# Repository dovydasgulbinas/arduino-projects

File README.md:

# arduino-projects
a series of majority of my arduino projects

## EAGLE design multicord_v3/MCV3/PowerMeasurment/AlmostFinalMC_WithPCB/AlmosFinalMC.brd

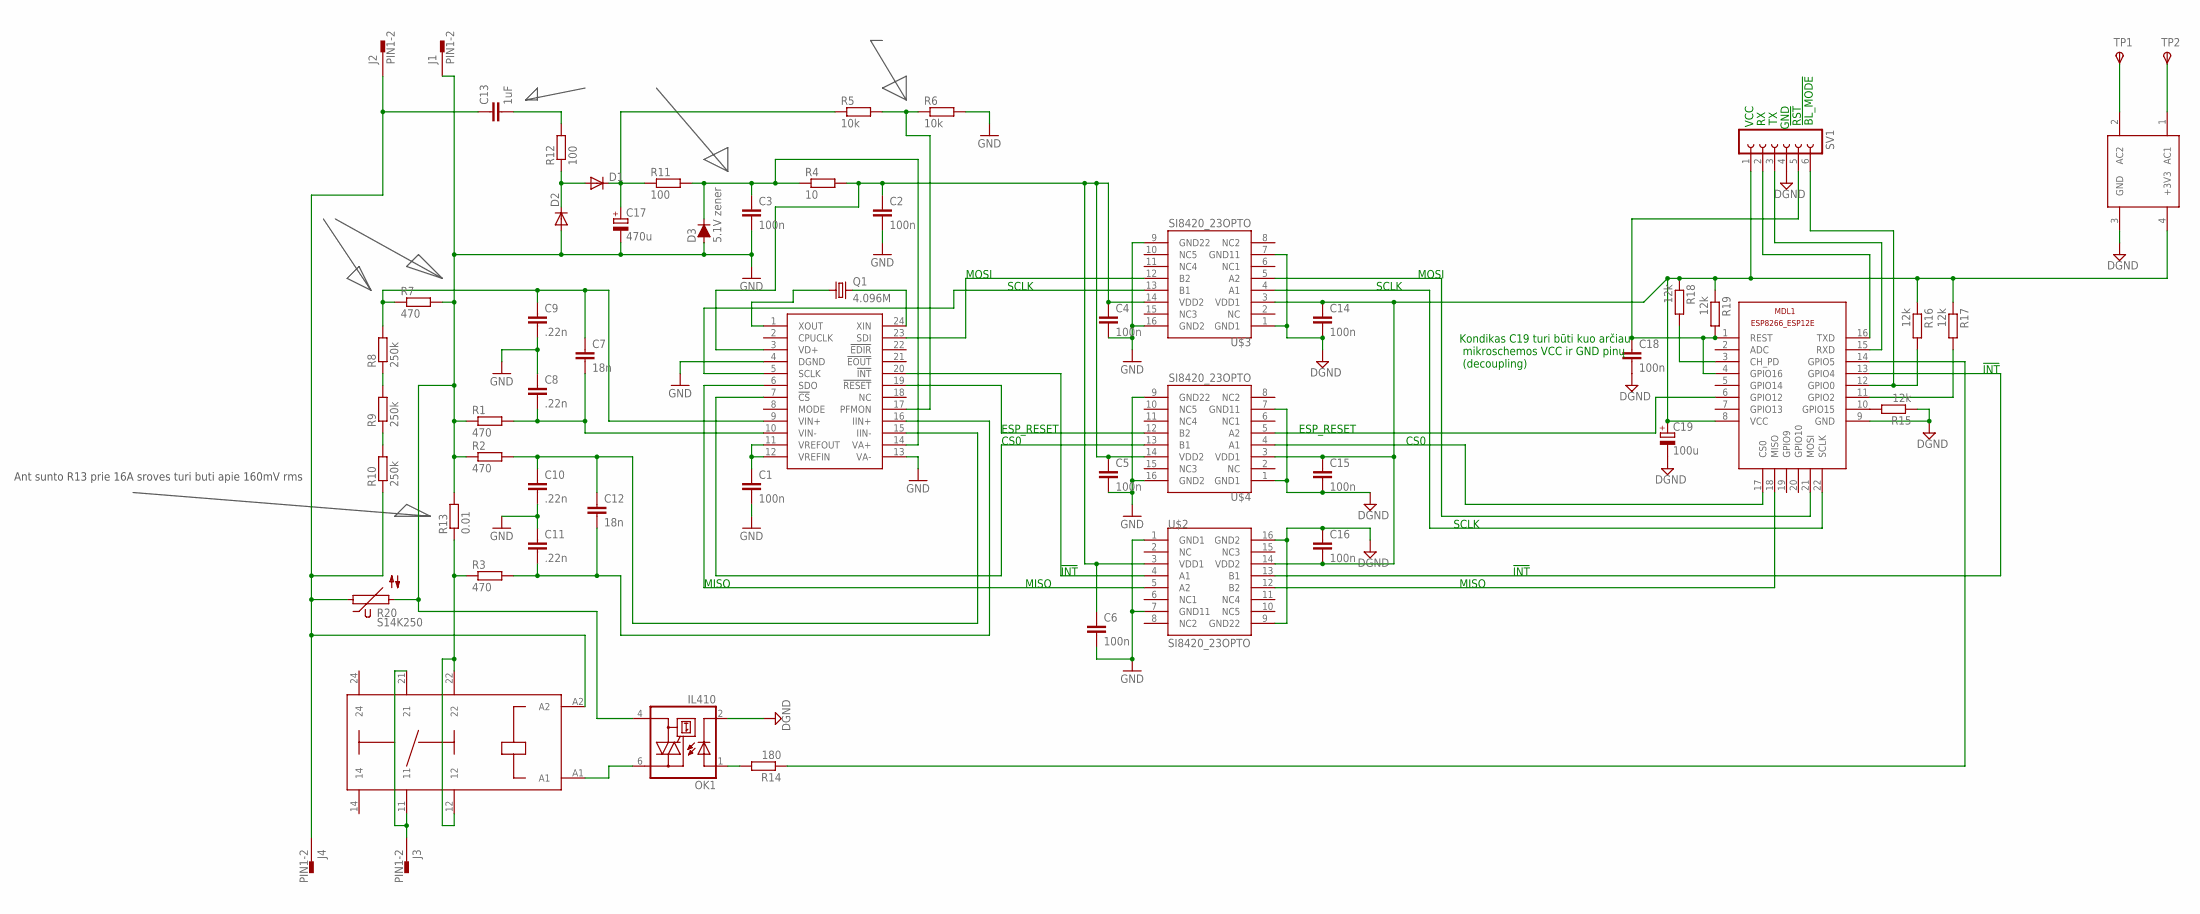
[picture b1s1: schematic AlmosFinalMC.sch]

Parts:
C1, C2, C3, C4, C5, C6, C14, C15, C16, C18: 100n; C0805
C7, C12: 18n; C0805
C8, C9, C10, C11: .22n; C0805
C13: 1uF; C225-113X268
C17: 470u; PANASONIC_G
C19: 100u; PANASONIC_G
D1, D2: DIODE-DO-214AC; DO-214AC
D3: 5.1V zener; SOD123
J1, J2, J3, J4: PIN1-2; 62221
MDL1: ESP8266-12EESP8266-ESP12E; ESP8266-ESP12E
OK1: IL410; DIL06
Q1: 4.096M; HC49UP
R1, R2, R3, R7: 470; R0805
R4: 10; R0805
R5, R6: 10k; R0805
R8, R9, R10: 250k; 0204/5
R11: 100; 0207/5V
R12: 100; 0309/10
R13: 0.01; RDH/15
R14: 180; R0805
R15, R16, R17, R18, R19: 12k; R0805
R20: S14K250
SV1: FE06-1; FE06
TP1, TP2: TPSPAD1-20Y; P1-20Y
U$1: CS5460A; SSOP24
U$2, U$3, U$4: SI8420_23OPTO; SI8420-SOIC8WB
U$5: RAC02
U$6: FINDER40-61

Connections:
DGND: C14.2, C15.2, C16.1, C18.2, C19.-, MDL1.9 (GND), OK1.2 (C), R15.1, SV1.4, U$2.9 (GND22), U$2.16 (GND2), U$3.1 (GND1), U$3.7 (GND11), U$4.1 (GND1), U$4.7 (GND11), U$5.3 (GND)
GND: C1.2, C2.2, C3.2, C4.2, C5.2, C6.2, C8.1, C9.2, C10.2, C11.1, C17.-, D2.A, D3.2 (A), J1.1, OK1.4 (A1), R1.1, R2.1, R6.2, R7.2, R13.2, R20.2, U$1.4 (DGND), U$1.13 (VA-), U$2.1 (GND1), U$2.7 (GND11), U$3.9 (GND22), U$3.16 (GND2), U$4.9 (GND22), U$4.16 (GND2)
unnamed: C3.1, D3.1 (C), R4.1, R11.2, U$1.14 (VA+)
unnamed: C2.1, C4.1, C5.1, C6.1, R4.2, U$1.3 (VD+), U$2.3 (VDD1), U$3.14 (VDD2), U$4.14 (VDD2)
unnamed: R5.2, R6.1, U$1.17 (PFMON)
unnamed: C7.1, C9.1, R7.1, R8.2, U$1.9 (VIN+)
unnamed: U$1.23 (SDI), U$3.12 (B2)
unnamed: C7.2, C8.2, R1.2, U$1.10 (VIN-)
unnamed: C17.+, D1.C, R5.1, R11.1
unnamed: D1.A, D2.C, R12.1
unnamed: MDL1.14 (GPIO5), R14.1
unnamed: C10.1, C12.1, R2.2, U$1.15 (IIN-)
unnamed: C11.2, C12.2, R3.2, U$1.16 (IIN+)
unnamed: MDL1.16 (TXD), SV1.2
unnamed: C1.1, U$1.11 (VREFOUT), U$1.12 (VREFIN)
unnamed: U$1.20 (!INT!), U$2.4 (A1)
unnamed: U$1.6 (SDO), U$2.5 (A2)
unnamed: R3.1, R13.1, U$6.12, U$6.22
unnamed: C13.1, J2.1, J4.1, R10.1, R20.1, U$6.A2
unnamed: R8.1, R9.2
unnamed: R9.1, R10.2
unnamed: C13.2, R12.2
unnamed: MDL1.6 (GPIO12), U$4.5 (A2)
unnamed: MDL1.15 (RXD), SV1.3
unnamed: U$1.7 (!CS!), U$4.13 (B1)
unnamed: U$1.5 (SCLK), U$3.13 (B1)
unnamed: U$1.19 (!RESET!), U$4.12 (B2)
unnamed: MDL1.10 (GPIO15), R15.2
unnamed: MDL1.11 (GPIO2), R17.2
unnamed: TP1.TP, U$5.2 (AC2)
unnamed: C14.1, C15.1, C16.2, C19.+, MDL1.8 (VCC), R16.1, R17.1, R18.1, R19.1, SV1.1, U$2.14 (VDD2), U$3.3 (VDD1), U$4.3 (VDD1), U$5.4 (+3V3)
unnamed: TP2.TP, U$5.1 (AC1)
unnamed: Q1.1, U$1.1 (XOUT)
unnamed: Q1.2, U$1.24 (XIN)
unnamed: MDL1.22 (SCLK), U$3.4 (A1)
unnamed: MDL1.17 (CS0), U$4.4 (A1)
unnamed: OK1.1 (A), R14.2
unnamed: MDL1.21 (MOSI), U$3.5 (A2)
unnamed: MDL1.3 (CH_PD), R18.2
unnamed: MDL1.18 (MISO), U$2.12 (B2)
unnamed: MDL1.13 (GPIO4), U$2.13 (B1)
unnamed: J3.1, U$6.11, U$6.21
unnamed: OK1.6 (A2), U$6.A1
unnamed: MDL1.12 (GPIO0), R16.2, SV1.6
unnamed: C18.1, MDL1.1 (REST), MDL1.4 (GPIO16), R19.2, SV1.5

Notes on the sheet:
Kondikas C19 turi būti kuo arčiau mikroschemos VCC ir GND pinų (decoupling)
MOSI
MISO
!INT!
VCC
GND
!BL_MODE!
!RST!
SCLK
ESP_RESET
CS0
Ant sunto R13 prie 16A sroves turi buti apie 160mV rms

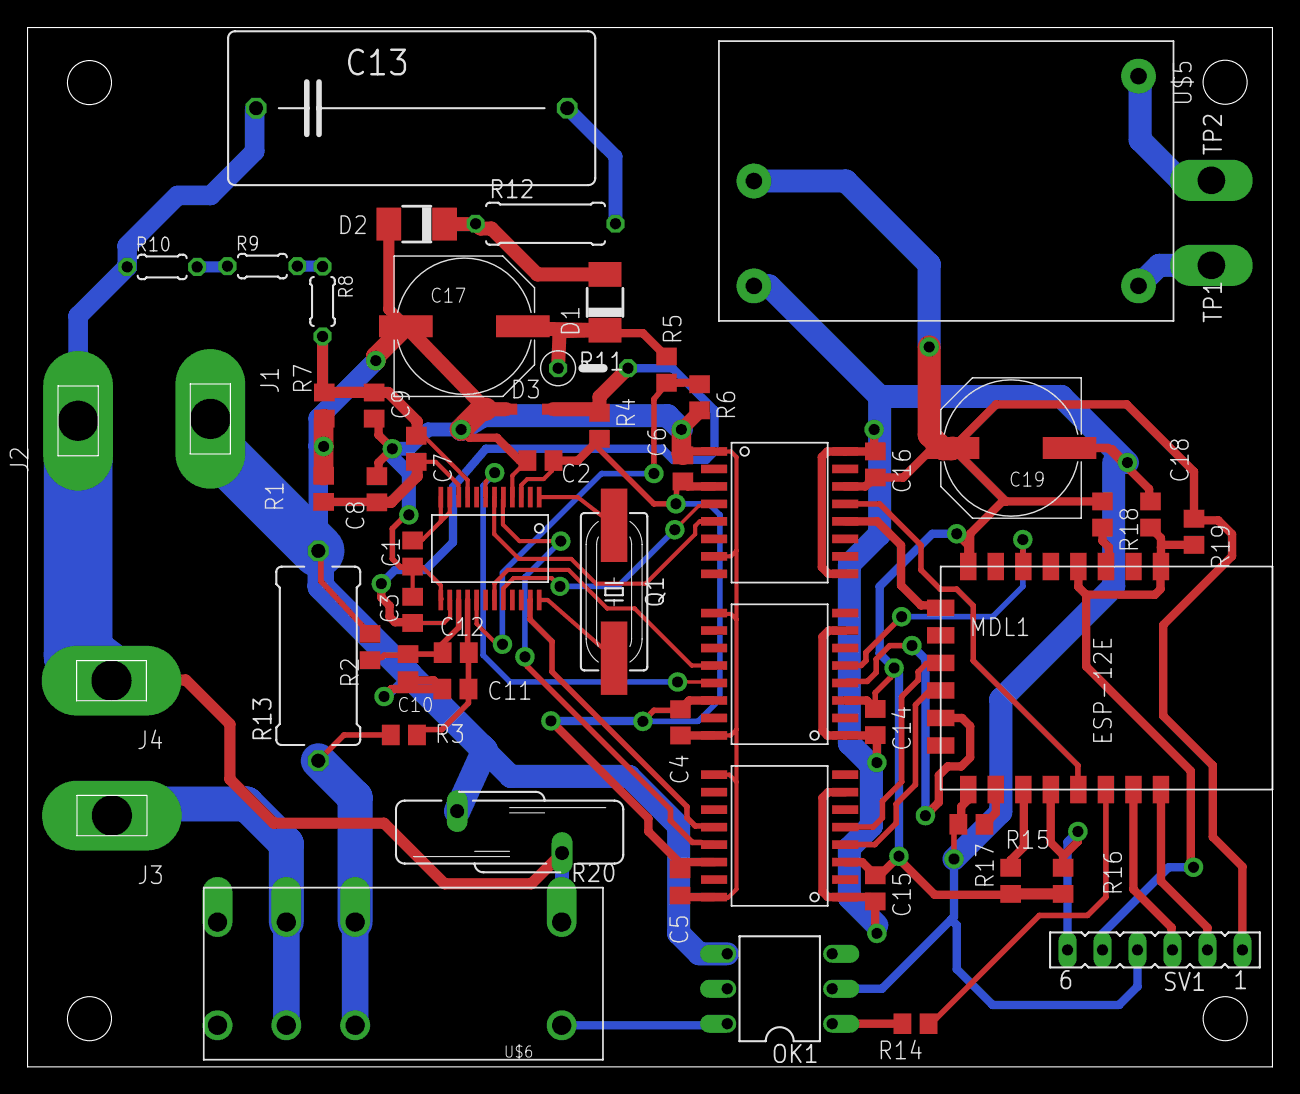
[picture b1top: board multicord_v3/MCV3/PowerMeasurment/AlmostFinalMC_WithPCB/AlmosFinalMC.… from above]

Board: 2 copper layers, 90.4 x 75.5 mm, 58 parts (0 on the bottom side), 45 nets.

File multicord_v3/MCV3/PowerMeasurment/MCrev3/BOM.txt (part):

Partlist exported from C:/Users/Daumantas/Desktop/MCrev3/AlmosFinalMC.sch at 2016-06-06 16:13

Part Value       Device                    Package           Description                                             MF                MPN   OC_FARNELL OC_NEWARK SPICEMODEL SPICEPREFIX TP_SIGNAL_NAME
C1   100n        CC0603                    C0603             CAPACITOR, European symbol                                                                           NONE       C                         
C2   100n        CC0603                    C0603             CAPACITOR, European symbol                                                                           NONE       C                         
C3   100n        CC0603                    C0603             CAPACITOR, European symbol                                                                           NONE       C                         
C4   100n        CC0603                    C0603             CAPACITOR, European symbol                                                                           NONE       C                         
C7   18n         CC0603                    C0603             CAPACITOR, European symbol                                                                           NONE       C                         
C8   .22n        CC0603                    C0603             CAPACITOR, European symbol                                                                           NONE       C                         
C9   .22n        CC0603                    C0603             CAPACITOR, European symbol                                                                           NONE       C                         
C10  .22n        CC0603                    C0603             CAPACITOR, European symbol                                                                           NONE       C                         
C11  .22n        CC0603                    C0603             CAPACITOR, European symbol                                                                           NONE       C                         
C12  18n         CC0603                    C0603             CAPACITOR, European symbol                                                                           NONE       C                         
C14  100n        CC0603                    C0603             CAPACITOR, European symbol                                                                           NONE       C                         
C17  470u        CPOL-EUG                  PANASONIC_G       POLARIZED CAPACITOR, European symbol                                                                                                      
C18  100n        CC0603                    C0603             CAPACITOR, European symbol                                                                           NONE       C                         
C19  100u        CPOL-EUUD-4X5,8           UD-4X5,8_NICHICON POLARIZED CAPACITOR, European symbol                                                                                                      
D1               DIODE-DO-214AC            DO-214AC          DIODE                                                                                                                                     
D2               DIODE-DO-214AC            DO-214AC          DIODE                                                                                                                                     
D3   5.1V zener  D-FILL-SOD123             SOD123            DIODE                                                                                                                                     
MDL1             ESP8266-12EESP8266-ESP12E ESP8266-ESP12E    ESP8266-12E with additional I/O and GPIO04/05 corrected                                                                                   
OK1  MOC3083     IL410                     DIL06             SIEMENS OPTO COUPLER                                    VISHAY/TELEFUNKEN IL410 1045434    58K1715                                        
Q1   4.096M      CRYSTALHC49UP             HC49UP            CRYSTAL                                                                         unknown    unknown                                        
R1   470         RR0603                    R0603             RESISTOR, European symbol                                                                            NONE       R                         
R2   470         RR0603                    R0603             RESISTOR, European symbol                                                                            NONE       R                         
R3   470         RR0603                    R0603             RESISTOR, European symbol                                                                            NONE       R                         
R4   5R1         R                         R0805             RESISTOR, European symbol                                                                            NONE       R                         
R5   10k         RR0603                    R0603             RESISTOR, European symbol                                                                            NONE       R                         
R6   10k         RR0603                    R0603             RESISTOR, European symbol                                                                            NONE       R                         
R7   470         R                         R0805             RESISTOR, European symbol                                                                            NONE       R                         
R8   250k        R-EU_0204/7               0204/7            RESISTOR, European symbol                                                                                                                 
R9   250k        R-EU_0204/7               0204/7            RESISTOR, European symbol                                                                                                                 
R10  250k        R-EU_0204/7               0204/7            RESISTOR, European symbol                                                                                                                 
R11  100         R-EU_0207/5V              0207/5V           RESISTOR, European symbol                                                                                                                 
R12  100         R-EU_0309/10              0309/10           RESISTOR, European symbol                                                                                                                 
R13  0.01        R-EU_V235/17              V235/17           RESISTOR, European symbol                                                                                                                 
R14  180         R-EU_R0603                R0603             RESISTOR, European symbol                                                                                                                 
R15  12k         RR0603                    R0603             RESISTOR, European symbol                                                                            NONE       R                         
R16  12k         RR0603                    R0603             RESISTOR, European symbol                                                                            NONE       R                         
R17  12k         RR0603                    R0603             RESISTOR, European symbol                                                                            NONE       R                         
R18  12k         RR0603                    R0603             RESISTOR, European symbol                                                                            NONE       R                         
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
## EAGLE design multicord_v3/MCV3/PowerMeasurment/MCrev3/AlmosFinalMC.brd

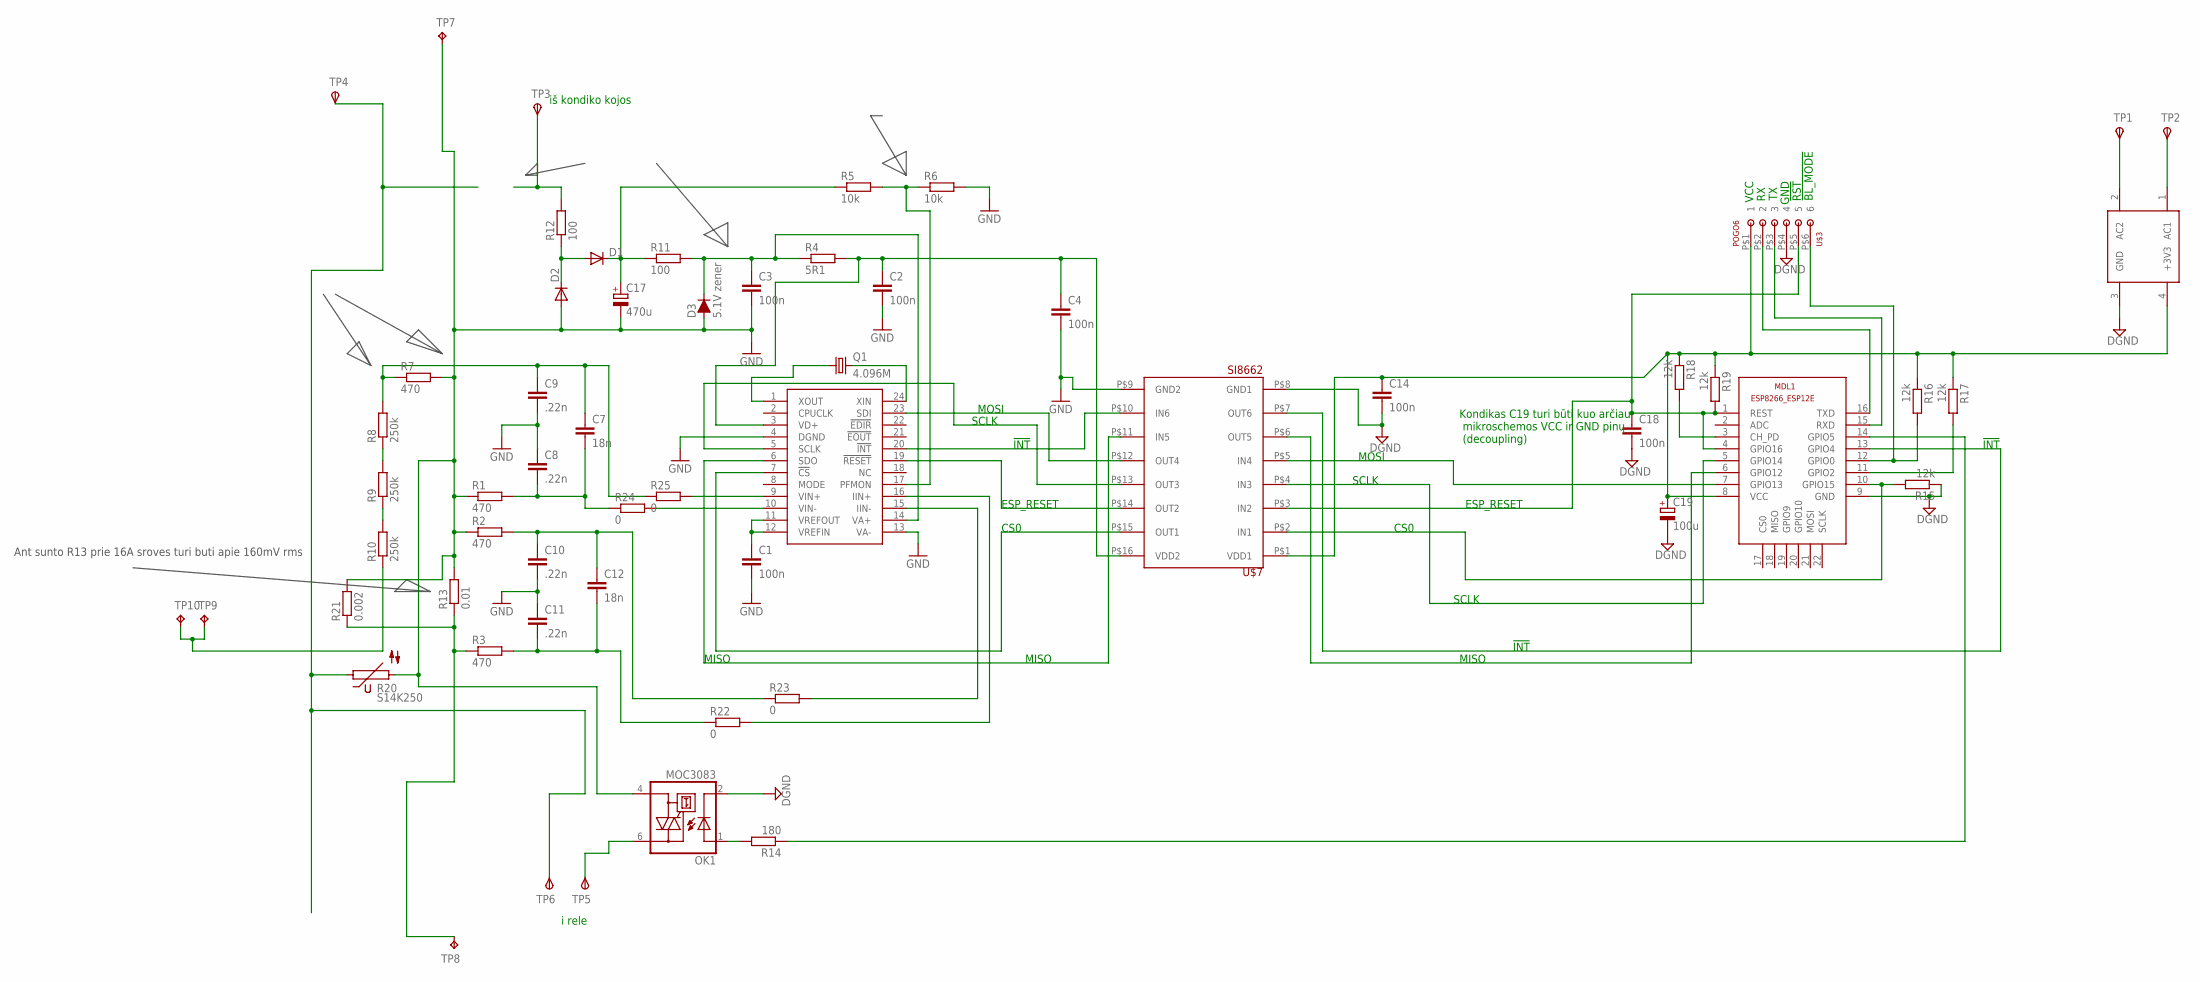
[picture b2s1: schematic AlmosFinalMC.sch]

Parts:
C1, C2, C3, C4, C14, C18: 100n; C0603
C7, C12: 18n; C0603
C8, C9, C10, C11: .22n; C0603
C17: 470u; PANASONIC_G
C19: 100u; UD-4X5,8_NICHICON
D1, D2: DIODE-DO-214AC; DO-214AC
D3: 5.1V zener; SOD123
MDL1: ESP8266-12EESP8266-ESP12E; ESP8266-ESP12E
OK1: MOC3083; DIL06
Q1: 4.096M; HC49UP
R1, R2, R3: 470; R0603
R4: 5R1; R0805
R5, R6: 10k; R0603
R7: 470; R0805
R8, R9, R10: 250k; 0204/7
R11: 100; 0207/5V
R12: 100; 0309/10
R13: 0.01; V235/17
R14: 180; R0603
R15, R16, R17, R18, R19: 12k; R0603
R20: S14K250
R21: 0.002; R2512
R22, R23, R24, R25: 0; R0603
TP1, TP2, TP3, TP4, TP5, TP6: TPSPAD1-13Y; P1-13Y
TP7, TP8: TPPAD1-20; P1-20
TP9, TP10: TPPAD1-13; P1-13
U$1: CS5460A; SSOP24
U$3: POGO6
U$5: RAC02
U$7: SI8662; SOIC8

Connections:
DGND: C14.2, C18.2, C19.-, MDL1.9 (GND), OK1.2 (C), R15.1, U$3.P$4 (4), U$5.3 (GND), U$7.P$8 (GND1)
GND: C1.2, C2.2, C3.2, C4.2, C8.1, C9.2, C10.2, C11.1, C17.-, D2.A, D3.2 (A), OK1.4 (A1), R1.1, R2.1, R6.2, R7.2, R13.2, R20.2, R21.2, TP7.TP, U$1.4 (DGND), U$1.13 (VA-), U$7.P$9 (GND2)
unnamed: C3.1, D3.1 (C), R4.1, R11.2, U$1.14 (VA+)
unnamed: C2.1, C4.1, R4.2, U$1.3 (VD+), U$7.P$16 (VDD2)
unnamed: R5.2, R6.1, U$1.17 (PFMON)
unnamed: C7.1, C9.1, R7.1, R8.2, R25.1
unnamed: U$1.23 (SDI), U$7.P$12 (OUT4)
unnamed: C7.2, C8.2, R1.2, R24.1
unnamed: C17.+, D1.C, R5.1, R11.1
unnamed: D1.A, D2.C, R12.1
unnamed: MDL1.14 (GPIO5), R14.1
unnamed: C10.1, C12.1, R2.2, R23.1
unnamed: R22.2, U$1.16 (IIN+)
unnamed: MDL1.16 (TXD), U$3.P$2 (2)
unnamed: C1.1, U$1.11 (VREFOUT), U$1.12 (VREFIN)
unnamed: U$1.20 (!INT!), U$7.P$10 (IN6)
unnamed: U$1.6 (SDO), U$7.P$11 (IN5)
unnamed: R3.1, R13.1, R21.1, TP8.TP
unnamed: R20.1, TP4.TP, TP6.TP
unnamed: R8.1, R9.2
unnamed: R9.1, R10.2
unnamed: R12.2, TP3.TP
unnamed: MDL1.6 (GPIO12), U$7.P$6 (OUT5)
unnamed: MDL1.15 (RXD), U$3.P$3 (3)
unnamed: U$1.7 (!CS!), U$7.P$15 (OUT1)
unnamed: U$1.5 (SCLK), U$7.P$13 (OUT3)
unnamed: U$1.19 (!RESET!), U$7.P$14 (OUT2)
unnamed: R23.2, U$1.15 (IIN-)
unnamed: MDL1.11 (GPIO2), R17.2
unnamed: TP1.TP, U$5.2 (AC2)
unnamed: C14.1, C19.+, MDL1.8 (VCC), R16.1, R17.1, R18.1, R19.1, U$3.P$1 (1), U$5.4 (+3V3), U$7.P$1 (VDD1)
unnamed: TP2.TP, U$5.1 (AC1)
unnamed: Q1.1, U$1.1 (XOUT)
unnamed: Q1.2, U$1.24 (XIN)
unnamed: MDL1.5 (GPIO14), U$7.P$4 (IN3)
unnamed: MDL1.10 (GPIO15), R15.2, U$7.P$2 (IN1)
unnamed: OK1.1 (A), R14.2
unnamed: MDL1.7 (GPIO13), U$7.P$5 (IN4)
unnamed: MDL1.3 (CH_PD), R18.2
unnamed: C11.2, C12.2, R3.2, R22.1
unnamed: MDL1.13 (GPIO4), U$7.P$7 (OUT6)
unnamed: R24.2, U$1.10 (VIN-)
unnamed: R25.2, U$1.9 (VIN+)
unnamed: OK1.6 (A2), TP5.TP
unnamed: MDL1.12 (GPIO0), R16.2, U$3.P$6 (6)
unnamed: R10.1, TP9.TP, TP10.TP
unnamed: C18.1, MDL1.1 (REST), MDL1.4 (GPIO16), R19.2, U$3.P$5 (5), U$7.P$3 (IN2)

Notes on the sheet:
Kondikas C19 turi būti kuo arčiau mikroschemos VCC ir GND pinų (decoupling)
MOSI
MISO
!INT!
VCC
GND
!BL_MODE!
!RST!
SCLK
ESP_RESET
CS0
Ant sunto R13 prie 16A sroves turi buti apie 160mV rms
iš kondiko kojos
i rele

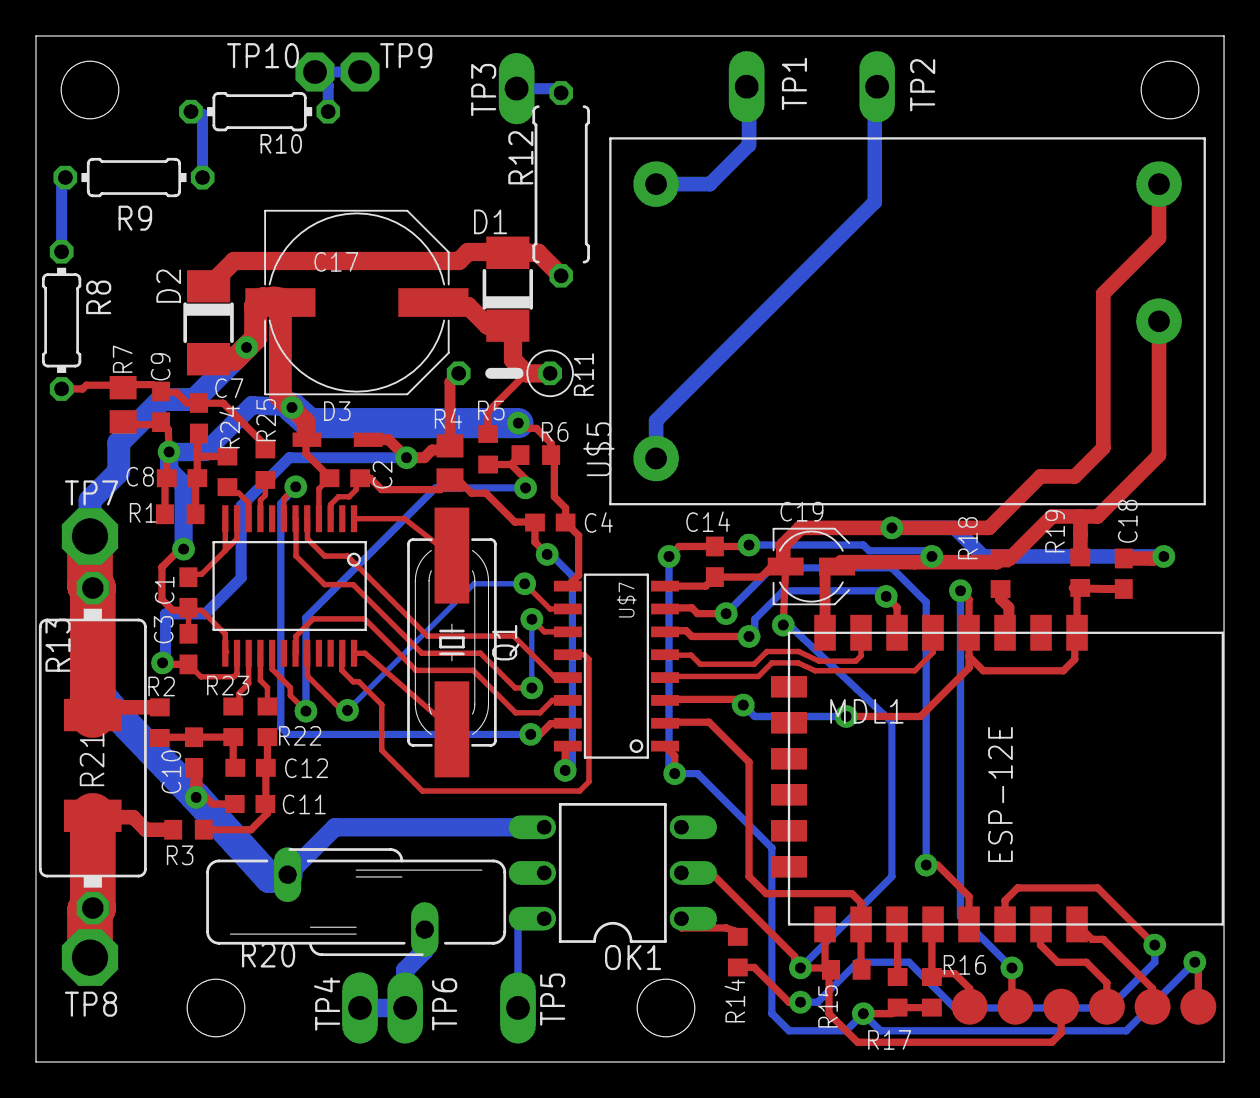
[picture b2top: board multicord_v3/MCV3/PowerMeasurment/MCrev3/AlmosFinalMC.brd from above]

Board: 2 copper layers, 66.0 x 57.0 mm, 59 parts (0 on the bottom side), 47 nets.

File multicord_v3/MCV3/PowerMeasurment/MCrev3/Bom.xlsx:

C1 | 100nF | 0603, minimum 25 V
C2 | 100nF | 0603, minimum 25 V
C3 | 100nF | 0603, minimum 25 V
C4 | 100nF | 0603, minimum 25 V
C7 | 18nF | 0603, minimum 25 V
C8 | 220pF | 0603, minimum 25 V
C9 | 220pF | 0603, minimum 25 V
C10 | 220pF | 0603, minimum 25 V
C11 | 220pF | 0603, minimum 25 V
C12 | 18nF | 0603, minimum 25 V
C14 | 100nF | 0603, minimum 25 V
C17 | 470uF | elektrol 25V, panasonic | EEE-1EA471P
C18 | 100nF | 0603, minimum 25 V
C19 | 100uF | elektrol 6.3V | 826629-6
C | 1uF | Film Capacitors 1.0uF 305Vac | B32923H3105M
D1 | S1J diode | DO-214AC korpusas | S1J
D2 | S1J diode | DO-214AC korpusas | S1J
D3 | 5.1V zener | Zener Diodes 5.1V 0.5W Zener | MMSZ4689
MDL1 | ESP8266 | WIFI modulis
OK1 | MOC3083 | optopora
Q1 | 4.096 MHz | Crystals 4.096MHz 30ppm -20 +70C 18pF | 9C-4.096MAAJ-T
R1 | 470 Ohm | 0603
R2 | 470 Ohm | 0603
R3 | 470 Ohm | 0603
R4 | 5.1 Ohm | 0805
R5 | 10 kOhm | 0603
R6 | 10 kOhm | 0603
R7 | 470 Ohm | 0805, 1%
R8 | 250 kOhm | Metal Film Resistors - Through Hole 1/4watt 250Kohms 1%
R9 | 250 kOhm | Metal Film Resistors - Through Hole 1/4watt 250Kohms 1%
R10 | 250 kOhm | Metal Film Resistors - Through Hole 1/4watt 250Kohms 1%
R11 | 100 Ohm | Metal Oxide Resistors 1/2W 100 5% | MOS1/2CT52R101J
R12 | 100 Ohm | Metal Oxide Resistors 1W 100 5% | MOS1CT52R101J
R14 | 180 Ohm | 0603
R15 | 12 kOhm | 0603
R16 | 12 kOhm | 0603
R17 | 12 kOhm | 0603
R18 | 12 kOhm | 0603
R19 | 12 kOhm | 0603
R20 | S14K250 | Varistor S14K250G5S5
R21 | 0.002 Ohm | 2512 korpuse, minimum 1W šuntas
R22 | 0 ohm | 0603
R23 | 0ohm | 0603
R24 | 0ohm | 0603
R25 | 0ohm | 0603
U1 | CS5460A | SSOP24, Current & Power Monitors & Regulators Single-Phase Bi-Dir Power/Energy 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
U5 | RAC02 | AC/DC Power Modules CONV AC/DC 2W 80-264VIN 3.3VOUT | RAC02-3.3SC
U7 | Si8662 | SOIC8
Relay | 40.61.8.230.0000 | Finder

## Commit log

2016-12-03 initial huge commit
2016-12-03 removing subdirs
2016-12-03 huge global commit
2016-12-03 Adding old git repos
2016-12-03 cleaning code_projects dir
